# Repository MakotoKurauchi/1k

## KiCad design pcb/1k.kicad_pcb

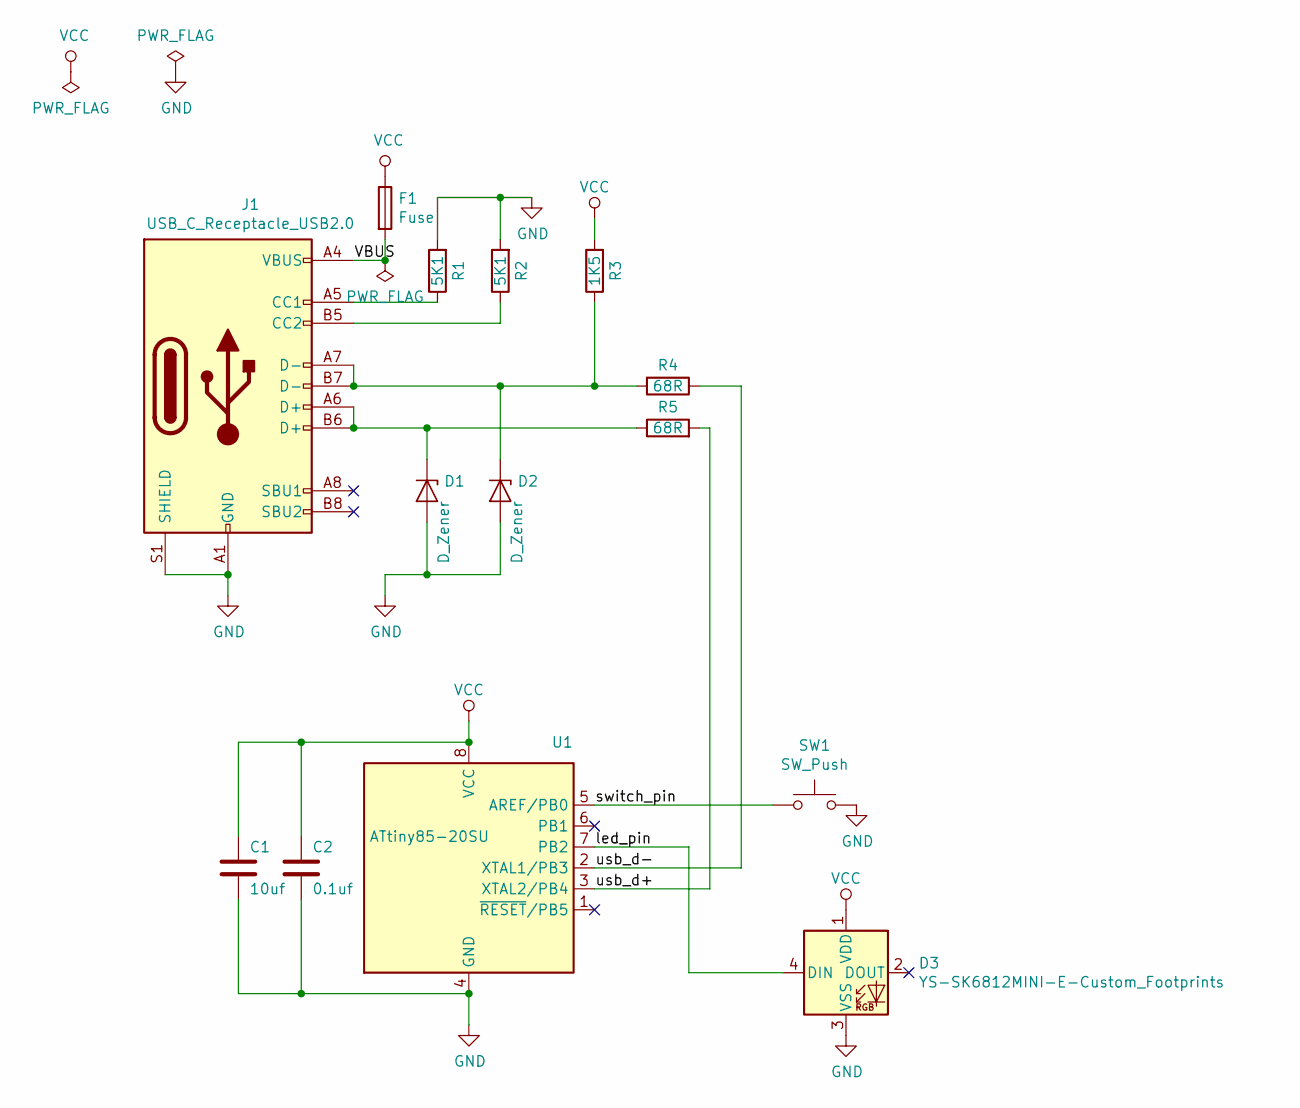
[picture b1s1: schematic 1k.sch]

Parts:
C1: 10uf; C_0402_1005Metric
C2: 0.1uf; C_0402_1005Metric
D1, D2: D_Zener; D_SOD-323
D3: YS-SK6812MINI-E-Custom_Footprints; YS-SK6812MINI-E_short
F1: Fuse; Fuse_0805_2012Metric
J1: USB_C_Receptacle_USB2.0; USB_C_Receptacle_HRO_TYPE-C-31-M-12
R1, R2: 5K1; R_0402_1005Metric
R3: 1K5; R_0402_1005Metric
R4, R5: 68R; R_0402_1005Metric
SW1: SW_Push; CherryMX_noLed
U1: ATtiny85-20SU; SOIJ-8_5.3x5.3mm_P1.27mm

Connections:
/VBUS: F1.2, J1.A4 (VBUS), J1.A9 (VBUS), J1.B4 (VBUS), J1.B9 (VBUS)
/led_pin: D3.4 (DIN), U1.7 (PB2)
/switch_pin: SW1.1, U1.5 (AREF/PB0)
/usb_d+: R5.2, U1.3 (XTAL2/PB4)
/usb_d-: R4.1, U1.2 (XTAL1/PB3)
GND: C1.2, C2.2, D1.2 (A), D2.2 (A), D3.3 (VSS), J1.A1 (GND), J1.A12 (GND), J1.B1 (GND), J1.B12 (GND), J1.S1 (SHIELD), R1.2, R2.2, SW1.2, U1.4 (GND)
unnamed: D1.1 (K), J1.A6 (D+), J1.B6 (D+), R5.1
unnamed: D2.1 (K), J1.A7 (D-), J1.B7 (D-), R3.1, R4.2
unnamed: J1.A5 (CC1), R1.1
unnamed: J1.B5 (CC2), R2.1
VCC: C1.1, C2.1, D3.1 (VDD), F1.1, R3.2, U1.8 (VCC)

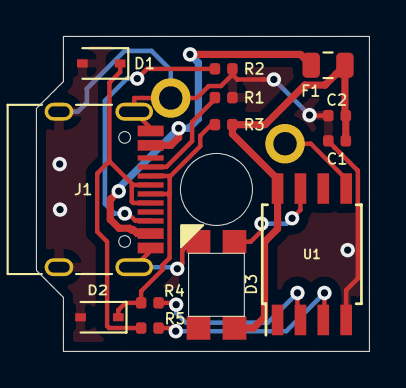
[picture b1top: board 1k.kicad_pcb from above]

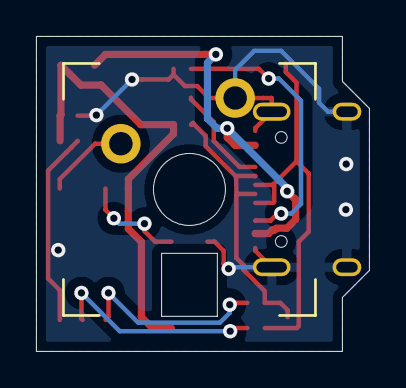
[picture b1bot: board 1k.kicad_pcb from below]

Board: 2 copper layers, 18.5 x 17.5 mm, 14 parts (2 on the bottom side), 11 nets.

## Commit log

2021-12-18 add buildguide
2021-12-21 add mac guide
2022-05-02 change url
2022-05-02 add pcb files
